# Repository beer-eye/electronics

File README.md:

# Electronics
PCB and Schematics

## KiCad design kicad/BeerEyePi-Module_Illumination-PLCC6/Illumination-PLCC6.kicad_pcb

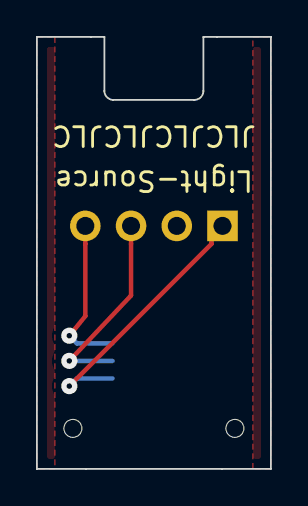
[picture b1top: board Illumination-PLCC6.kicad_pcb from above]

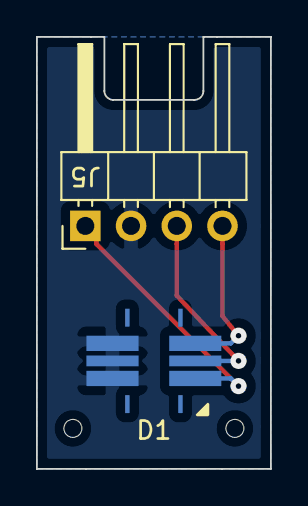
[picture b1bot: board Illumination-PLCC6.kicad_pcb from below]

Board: 2 copper layers, 13.0 x 24.0 mm, 4 parts (2 on the bottom side), 4 nets.

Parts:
D1: LED_RGB; PLCC6-3528
H1, H2: RecoveryHole; Drill_1.0mm
J5: RGB_LED; PinHeader_1x04_P2.54mm_Horizontal

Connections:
/PLCC6_ANODE: D1.4, D1.5, D1.6, J5.2
unnamed: D1.1, J5.1
unnamed: D1.2, J5.3
unnamed: D1.3, J5.4

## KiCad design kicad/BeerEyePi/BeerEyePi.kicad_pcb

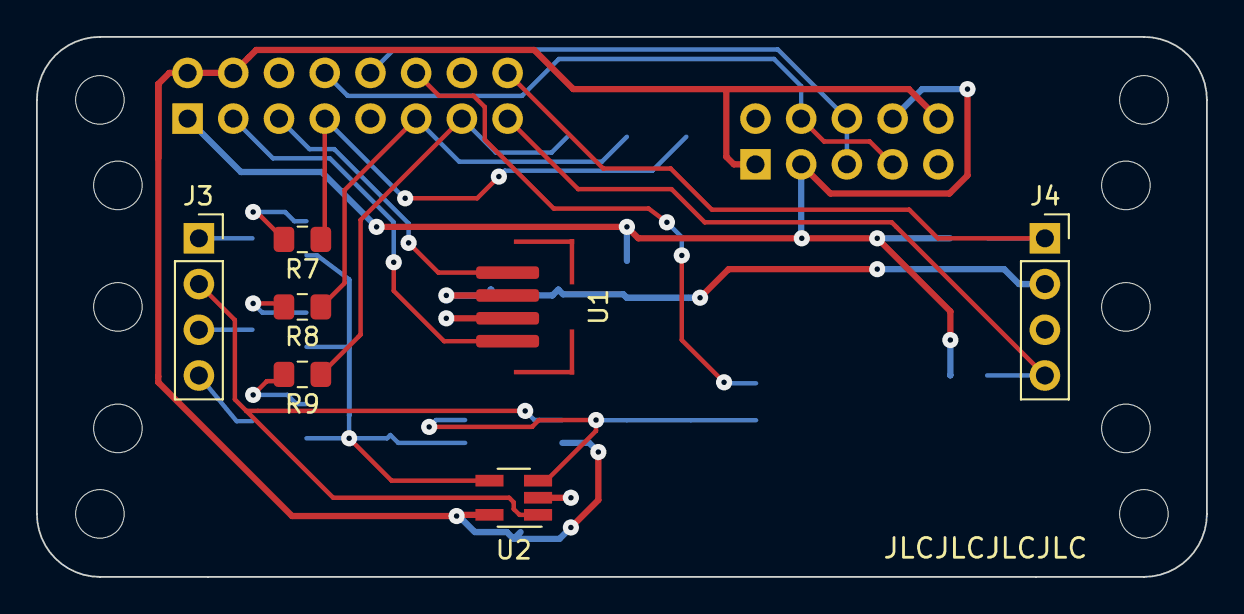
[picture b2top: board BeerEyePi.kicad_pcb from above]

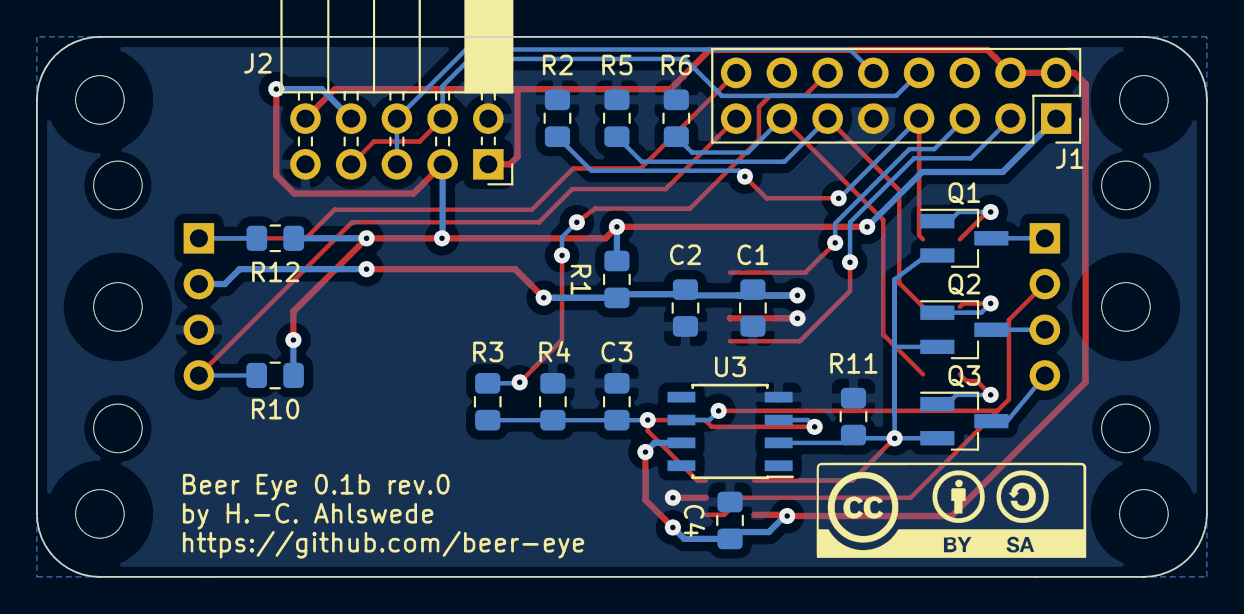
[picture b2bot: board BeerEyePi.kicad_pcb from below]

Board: 2 copper layers, 65.0 x 30.0 mm, 31 parts (19 on the bottom side), 23 nets.

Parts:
A1: Photometer
C1, C4: 100n; C_0805_2012Metric_Pad1.15x1.40mm_HandSolder
C2, C3: 10u; C_0805_2012Metric_Pad1.15x1.40mm_HandSolder
J1: RaspberryPi; PinSocket_2x08_P2.54mm_Vertical
J2: Extension; PinSocket_2x05_P2.54mm_Horizontal
J3: RGB_LED; PinSocket_1x04_P2.54mm_Vertical
J4: TransSensor; PinSocket_1x04_P2.54mm_Vertical
MH1, MH2, MH3, MH4: MountingHole M2.5; MountingHole_2.7mm_M2.5
Q1, Q2, Q3: CPH3456; SOT-23_Handsoldering
R1, R11: 15; R_0805_2012Metric_Pad1.15x1.40mm_HandSolder
R2, R3, R5, R6, R7, R8, R9: 33k; R_0805_2012Metric_Pad1.15x1.40mm_HandSolder
R4, R10, R12: 3.3k; R_0805_2012Metric_Pad1.15x1.40mm_HandSolder
U1: VEML7700; VEML7700_HandSoldering
U2: OPA340NA; SOT-23-5_HandSoldering
U3: OPA340UA; SOIC-8_3.9x4.9mm_P1.27mm

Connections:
+3.3VADC: C1.2, C2.2, J4.2, R1.2, U1.2
+3V3: J1.1, J2.3, J2.8, R1.1, R10.1, R12.1
+5V: C4.1, J1.2, J1.4, J2.1, J2.10, U2.5, U3.7
GND: C1.1, C2.1, C3.1, C4.2, J1.9, J2.2, J2.9, J4.3, R2.2, R4.2, R5.2, R6.2, R11.2, U1.3, U2.2, U3.4
LED1: J1.7, R2.1, R7.1
LED2: J1.11, R5.1, R8.1
LED3: J1.13, R6.1, R9.1
LED_CURRENT: J1.12, R3.1
unnamed: C3.2, R3.2, R4.1, U2.3, U3.3
unnamed: J3.1, Q1.3
unnamed: J3.2, U2.1, U3.6
unnamed: J3.3, Q2.3
unnamed: J3.4, Q3.3
unnamed: Q1.1, R7.2
unnamed: Q1.2, Q2.2, Q3.2, R11.1, U2.4, U3.2
unnamed: Q2.1, R8.2
unnamed: Q3.1, R9.2
RXD: J1.10, J2.5, J2.6
SCL1: J1.16, J4.1, R12.2
SCL2: J1.5, U1.1
SDA1: J1.15, J4.4, R10.2
SDA2: J1.3, U1.4
TXD: J1.8, J2.4, J2.7

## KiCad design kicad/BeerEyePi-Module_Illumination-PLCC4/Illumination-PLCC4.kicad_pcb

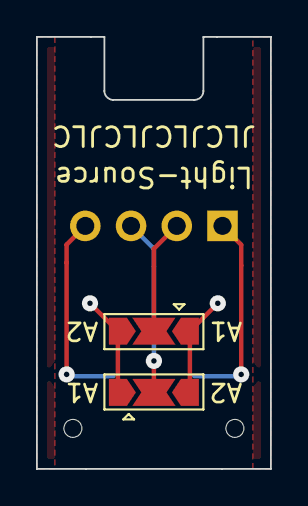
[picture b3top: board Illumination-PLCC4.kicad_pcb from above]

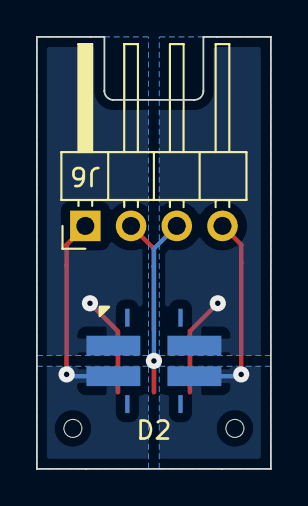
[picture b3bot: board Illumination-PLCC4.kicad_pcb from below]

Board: 2 copper layers, 13.0 x 24.0 mm, 6 parts (2 on the bottom side), 6 nets.

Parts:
D2: LED_ABGR; PLCC4-3528
H5, H6: RecoveryHole; Drill_1.0mm
J6: RGB_LED; PinHeader_1x04_P2.54mm_Horizontal
JP1: CA2; SolderJumper-3_P2.0mm_Open_TrianglePad1.0x1.5mm
JP2: CA1; SolderJumper-3_P2.0mm_Open_TrianglePad1.0x1.5mm

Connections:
/PLCC4_1: D2.1, JP1.1, JP2.3
/PLCC4_2: D2.2, JP1.3, JP2.1
/PLCC4_3: D2.3, J6.4
/PLCC4_4: D2.4, J6.1
unnamed: J6.2, JP1.2
unnamed: J6.3, JP2.2

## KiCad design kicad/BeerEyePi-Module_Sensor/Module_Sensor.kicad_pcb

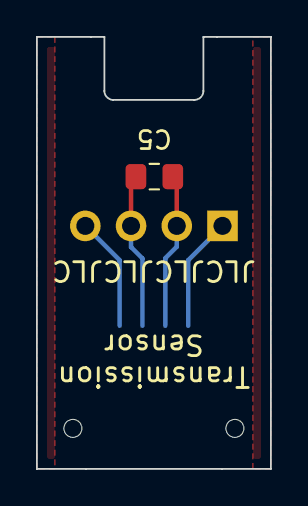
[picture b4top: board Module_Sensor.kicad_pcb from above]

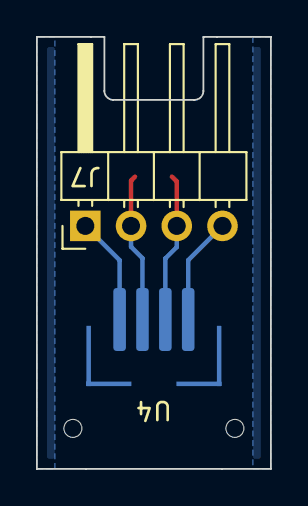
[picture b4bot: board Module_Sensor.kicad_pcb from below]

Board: 2 copper layers, 13.0 x 24.0 mm, 5 parts (2 on the bottom side), 4 nets.

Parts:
C5: 100n; C_0805_2012Metric_Pad1.15x1.40mm_HandSolder
H3, H4: RecoveryHole; Drill_1.0mm
J7: TransSensor; PinHeader_1x04_P2.54mm_Horizontal
U4: VEML7700; VEML7700_HandSoldering

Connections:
unnamed: C5.1, J7.2, U4.3
unnamed: C5.2, J7.3, U4.2
unnamed: J7.1, U4.4
unnamed: J7.4, U4.1

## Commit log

2019-04-05 Fixed flawed pin socket orientation for sensor module. Generated gerber files.
2019-04-07 Modules are individual KiCAD projects now.
